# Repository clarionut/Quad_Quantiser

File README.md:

# Quad_Quantiser

The original inspiration for this project came from the [Dual Quantizer by Hagiwo](https://note.com/solder_state/n/nb8b9a2f212a2), in particular the use of an RP2040 microcontroller and the general style of the OLED display / rotary encoder user interface. There the resemblance pretty much ends.

This project uses a WaveShare RP2040 Zero board as the processor, a MAX5715 12-bit 4-channel SPI DAC buffered and amplified to give a 5-octave output range on each of the four channels, plus a 24LC04 I2C EEPROM to allow the configuration to be saved. Both cores of the RP2040 are used with core 0 handling the analogue inputs, quantisation and output to the MAX5715, while core 1 handles the rotary encoder / 0.96" I2C OLED screen user interface and also the EEPROM.

There is a trigger input (common to all channels) plus CV and trigger outputs for each individual channel. The trigger input is monitored by an interrupt rather than by polling, so fast triggers should be acceptable. The channels can be independently configured to change the CV output and generate a trigger when:
- a trigger is received even if the quantisation is unchanged (TRIG)
- the quantisation of an input changes (NOTE)
- a trigger is received _and_ the quantisation has changed (T&&N)
- a trigger is received _or_ the quantisation changes (T||N)

The code is intended for use in the Arduino IDE (v 2.x) using the Waveshare RP2040 Zero core. RP2040_Quantizer6.ino and MAX5715.h should both be in the sketch folder.

The Kicad schematic includes custom symbols and footprints for the RP2040 Zero and for the MAX5715. The PCB layout is for a board to be mounted on brackets perpendicular to the front panel, and also includes custom footprints for the RP2040, MAX5715 and the power connector. I've also included a STEP file model of the RP2040 board for use with the Kicad 3D viewer. Note that the WaveShare Rp2040 Zero board does not have a reset connection broken out - I soldered a very thin wire from the RESET pad on the main PCB to one of the pads on the RP2040 Zero's Reset switch

At present the quantisation is limited to the conventional western 12-semitone scale. One obvious extension is to include less conventional scales - e.g. quarter tone or Bohlen-Pierce.

This design and its associated software are published under the Creative Commons Attribution-ShareAlike 4.0 International (CC BY-SA) 4.0 Deed.

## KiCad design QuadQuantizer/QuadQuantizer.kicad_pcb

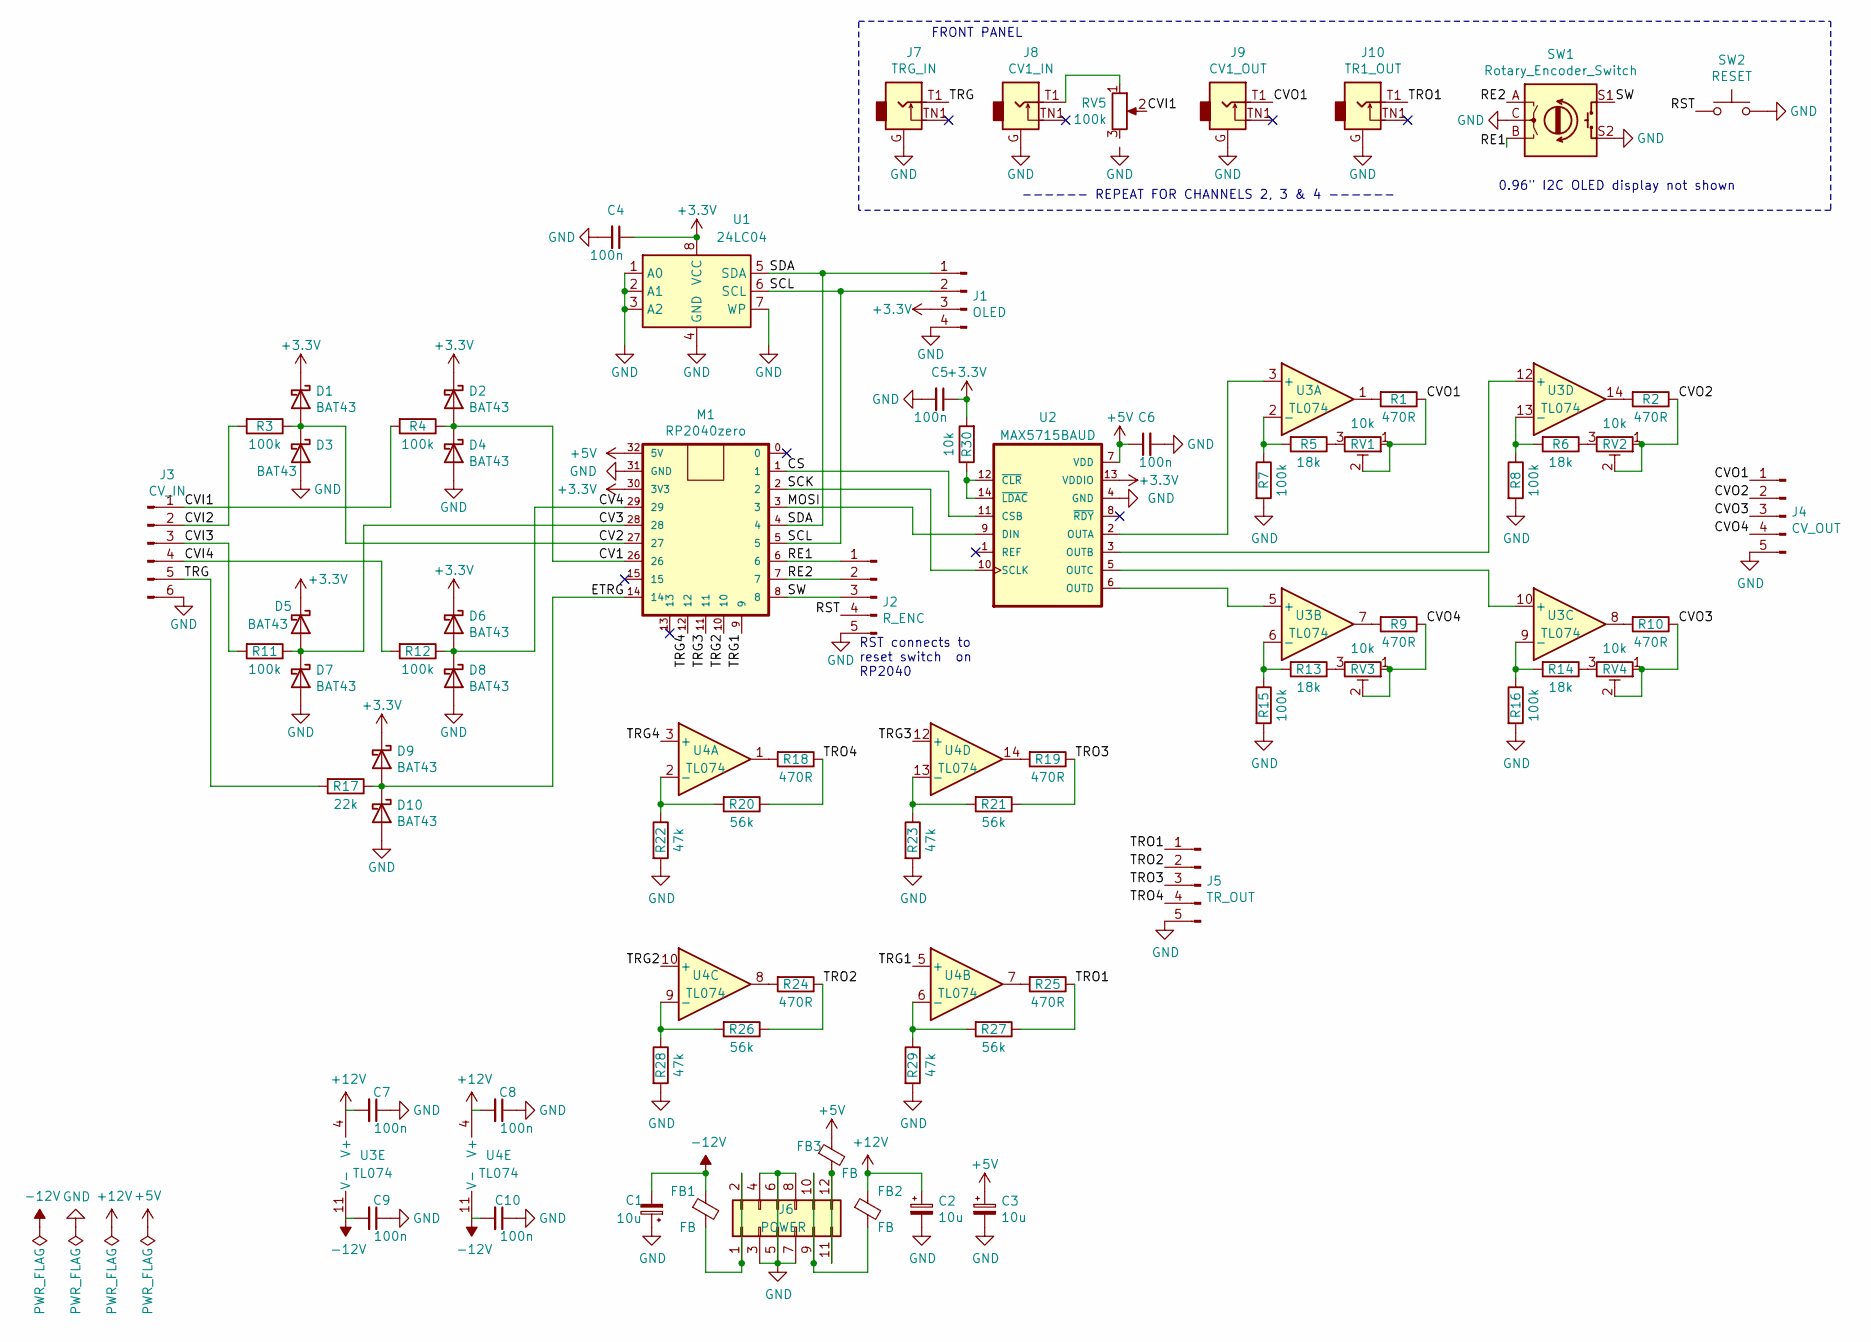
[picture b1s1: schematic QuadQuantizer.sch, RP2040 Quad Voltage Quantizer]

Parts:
C1, C2, C3: 10u; CP_Radial_D5.0mm_P2.50mm
C4, C5, C6, C7, C8, C9, C10: 100n; C_Disc_D4.3mm_W1.9mm_P5.00mm
D1, D2, D3, D4, D5, D6, D7, D8, D9, D10: BAT43; D_DO-34_SOD68_P7.62mm_Horizontal
FB1, FB2, FB3: FB; L_Axial_L5.3mm_D2.2mm_P7.62mm_Horizontal_Vishay_IM-1
J1: OLED; PinHeader_1x04_P2.54mm_Vertical
J2: R_ENC; PinHeader_1x05_P2.54mm_Vertical
J3: CV_IN; PinHeader_1x06_P2.54mm_Vertical
J4: CV_OUT; PinHeader_1x05_P2.54mm_Vertical
J5: TR_OUT; PinHeader_1x05_P2.54mm_Vertical
J6: POWER; Power_2x06
J7: TRG_IN
J8: CV1_IN
J9: CV1_OUT
J10: TR1_OUT
M1: RP2040zero; RP2040zeroA
R1, R2, R9, R10, R18, R19, R24, R25: 470R; R_Axial_DIN0204_L3.6mm_D1.6mm_P7.62mm_Horizontal
R3, R4, R7, R8, R11, R12, R15, R16: 100k; R_Axial_DIN0204_L3.6mm_D1.6mm_P7.62mm_Horizontal
R5, R6, R13, R14: 18k; R_Axial_DIN0204_L3.6mm_D1.6mm_P7.62mm_Horizontal
R17: 22k; R_Axial_DIN0204_L3.6mm_D1.6mm_P7.62mm_Horizontal
R20, R21, R26, R27: 56k; R_Axial_DIN0204_L3.6mm_D1.6mm_P7.62mm_Horizontal
R22, R23, R28, R29: 47k; R_Axial_DIN0204_L3.6mm_D1.6mm_P7.62mm_Horizontal
R30: 10k; R_Axial_DIN0204_L3.6mm_D1.6mm_P7.62mm_Horizontal
RV1, RV2, RV3, RV4: 10k; Potentiometer_Bourns_3296W_Vertical
RV5: 100k
SW1: Rotary_Encoder_Switch
SW2: RESET
U1: 24LC04; DIP-8_W7.62mm_Socket
U2: MAX5715BAUD; SOP-14-1EP_4.4x5mm_P0.65mm_EP3.4x5mm
U3, U4: TL074; DIP-14_W7.62mm_Socket

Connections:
+3V3: C4.1, C5.1, D1.1 (K), D2.1 (K), D5.1 (K), D6.1 (K), D9.1 (K), J1.3, M1.30 (3V3), R30.2, U1.8 (VCC), U2.13 (VDDIO)
+5V: C3.1, C6.1, FB3.1, M1.32 (5V), U2.7 (VDD)
+12V: C2.1, C7.2, C8.2, FB2.1, U3.4 (V+), U4.4 (V+)
-12V: C1.2, C9.2, C10.2, FB1.1, U3.11 (V-), U4.11 (V-)
/CS: M1.1, U2.11 (CSB)
/CV1: D2.2 (A), D4.1 (K), M1.26, R4.1
/CV2: D1.2 (A), D3.1 (K), M1.27, R3.1
/CV3: D5.2 (A), D7.1 (K), M1.28, R11.1
/CV4: D6.2 (A), D8.1 (K), M1.29, R12.1
/CVI1: J3.1, R4.2, RV5.2
/CVI2: J3.2, R3.2
/CVI3: J3.3, R11.2
/CVI4: J3.4, R12.2
/CVO1: J4.1, J9.T1, R1.1, RV1.1, RV1.2
/CVO2: J4.2, R2.1, RV2.1, RV2.2
/CVO3: J4.3, R10.1, RV4.1, RV4.2
/CVO4: J4.4, R9.1, RV3.1, RV3.2
/ETRG: D9.2 (A), D10.1 (K), M1.14, R17.1
/MOSI: M1.3, U2.9 (DIN)
/RE1: J2.1, M1.6, SW1.B
/RE2: J2.2, M1.7, SW1.A
/RST: J2.4, SW2.1; also elsewhere on the board
/SCK: M1.2, U2.10 (SCLK)
/SCL: J1.2, M1.5, U1.6 (SCL)
/SDA: J1.1, M1.4, U1.5 (SDA)
/SW: J2.3, M1.8, SW1.S1
/TRG: J3.5, J7.T1, R17.2
/TRG1: M1.9, U4.5 (+)
/TRG2: M1.10, U4.10 (+)
/TRG3: M1.11, U4.12 (+)
/TRG4: M1.12, U4.3 (+)
/TRO1: J5.1, J10.T1, R25.1, R27.1
/TRO2: J5.2, R24.1, R26.1
/TRO3: J5.3, R19.1, R21.1
/TRO4: J5.4, R18.1, R20.1
GND: C1.1, C2.2, C3.2, C4.2, C5.2, C6.2, C7.1, C8.1, C9.1, C10.1, D3.2 (A), D4.2 (A), D7.2 (A), D8.2 (A), D10.2 (A), J1.4, J2.5, J3.6, J4.5, J5.5, J6.3, J6.4, J6.5, J6.6, J6.7, J6.8, J7.G, J8.G, J9.G, J10.G, M1.31 (GND), R7.2, R8.2, R15.2, R16.2, R22.2, R23.2, R28.2, R29.2, SW1.C, SW1.S2, SW2.2, U1.1 (A0), U1.2 (A1), U1.3 (A2), U1.4 (GND), U1.7 (WP), U2.4 (GND)
unnamed: FB1.2, J6.1, J6.2
unnamed: FB2.2, J6.9, J6.10
unnamed: FB3.2, J6.11, J6.12
unnamed: J8.T1, RV5.1
unnamed: R1.2, U3.1
unnamed: R2.2, U3.14
unnamed: R5.1, RV1.3
unnamed: R5.2, R7.1, U3.2 (-)
unnamed: R6.1, RV2.3
unnamed: R6.2, R8.1, U3.13 (-)
unnamed: R9.2, U3.7
unnamed: R10.2, U3.8
unnamed: R13.1, RV3.3
unnamed: R13.2, R15.1, U3.6 (-)
unnamed: R14.1, RV4.3
unnamed: R14.2, R16.1, U3.9 (-)
unnamed: R18.2, U4.1
unnamed: R19.2, U4.14
unnamed: R20.2, R22.1, U4.2 (-)
unnamed: R21.2, R23.1, U4.13 (-)
unnamed: R24.2, U4.8
unnamed: R25.2, U4.7
unnamed: R26.2, R28.1, U4.9 (-)
unnamed: R27.2, R29.1, U4.6 (-)
unnamed: R30.1, U2.12 (~CLR), U2.14 (~LDAC)
unnamed: U2.2 (OUTA), U3.3 (+)
unnamed: U2.3 (OUTB), U3.12 (+)
unnamed: U2.5 (OUTC), U3.10 (+)
unnamed: U2.6 (OUTD), U3.5 (+)

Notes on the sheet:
RST connects to reset switch on RP2040
------ REPEAT FOR CHANNELS 2, 3 & 4 ------
0.96" I2C OLED display not shown
FRONT PANEL

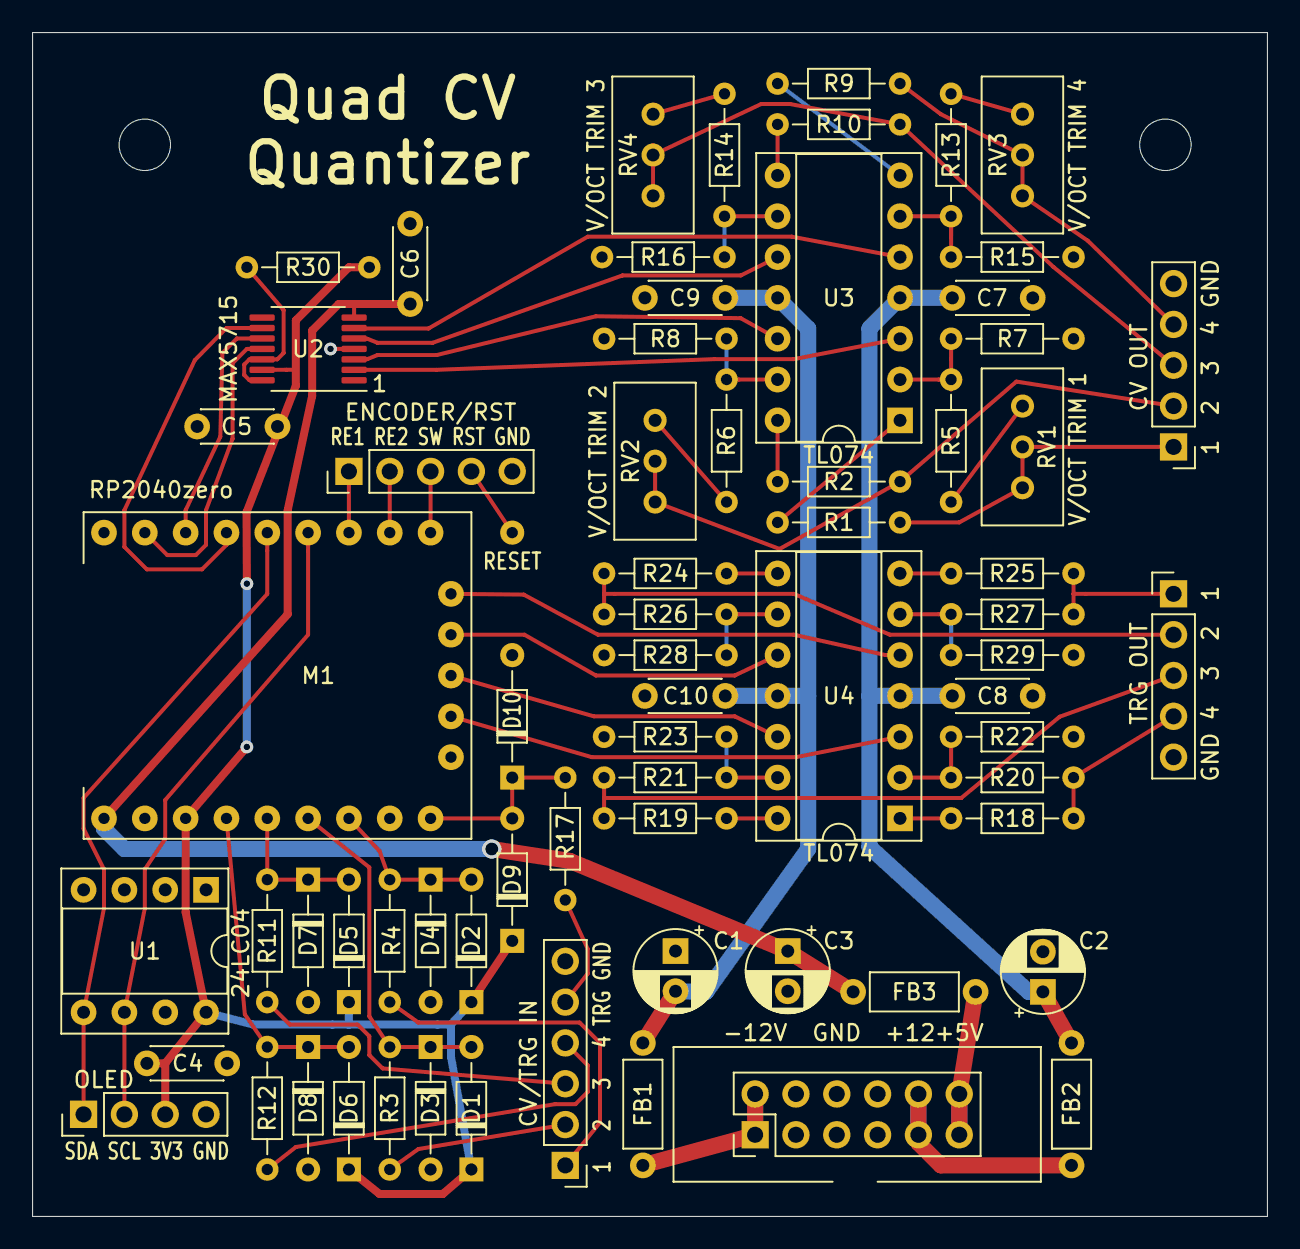
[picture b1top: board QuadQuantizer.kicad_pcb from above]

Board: 2 copper layers, 76.8 x 73.7 mm, 69 parts (0 on the bottom side), 64 nets.

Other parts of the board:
RST: RST; TestPoint_THTPad_D1.5mm_Drill0.7mm

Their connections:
/RST: RST.1; also elsewhere on the board

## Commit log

2023-10-29 Update README.md
    A quadruple CV quantizer for use in a modular synthesiser
2024-06-23 Create temp
